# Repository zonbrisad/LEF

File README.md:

<div style="text-align: center">

# LEF (Lightweigth Event Framework)

</div>

<!-- START doctoc generated TOC please keep comment here to allow auto update -->
<!-- DON'T EDIT THIS SECTION, INSTEAD RE-RUN doctoc TO UPDATE -->

  - [About](#about)
  - [Features](#features)
  - [Requirements](#requirements)
    - [Runtime](#runtime)
    - [Development](#development)
  - [Install](#install)
    - [Download](#download)
    - [Installation](#installation)
  - [Freqlenty asked Questions](#freqlenty-asked-questions)
  - [Links](#links)
  - [Contribute](#contribute)
  - [License](#license)
  - [Some examples, remove after creation](#some-examples-remove-after-creation)
- [The largest heading](#the-largest-heading)
  - [The second largest heading](#the-second-largest-heading)
          - [The smallest heading](#the-smallest-heading)
  - [Tables](#tables)
  - [List](#list)
  - [Task list](#task-list)
  - [Colapsed section](#colapsed-section)
      - [We can hide anything, even code!](#we-can-hide-anything-even-code)
  - [Links](#links-1)

<!-- END doctoc generated TOC please keep comment here to allow auto update -->

## About

Lightweigth Event Framework (LEF) is a software framework for small to medium sized microcontrollers. It is intended for applications where an RTOS would be overkill, but still deliver some level of convenience.

## Features

Components for:
 - LED
 - RG LED
 - Buzzer
 - Click Button
 - Potentiometer
 - Rotary encoder (experimental)
 - Cli
 - Timers (software)
 - Eventloop
 - Eventqueue

## Requirements

### Runtime

### Development

## Install

### Download

### Installation

### Configuration

## Freqlenty asked Questions

## History

[HISTORY.md](/HISTORY.md)

## ToDo

- Some sort of sequence class could be usefull.
- Membrane button scanner
- Use C23 when available
- Helper functions for argument parsing in CLI
- Improved filtering out ANSI terminal sequences
- PWM component
- Error handling via messages
- Timed queue, where an queueelement is sent after a certain time

## Links

## Contribute

## License

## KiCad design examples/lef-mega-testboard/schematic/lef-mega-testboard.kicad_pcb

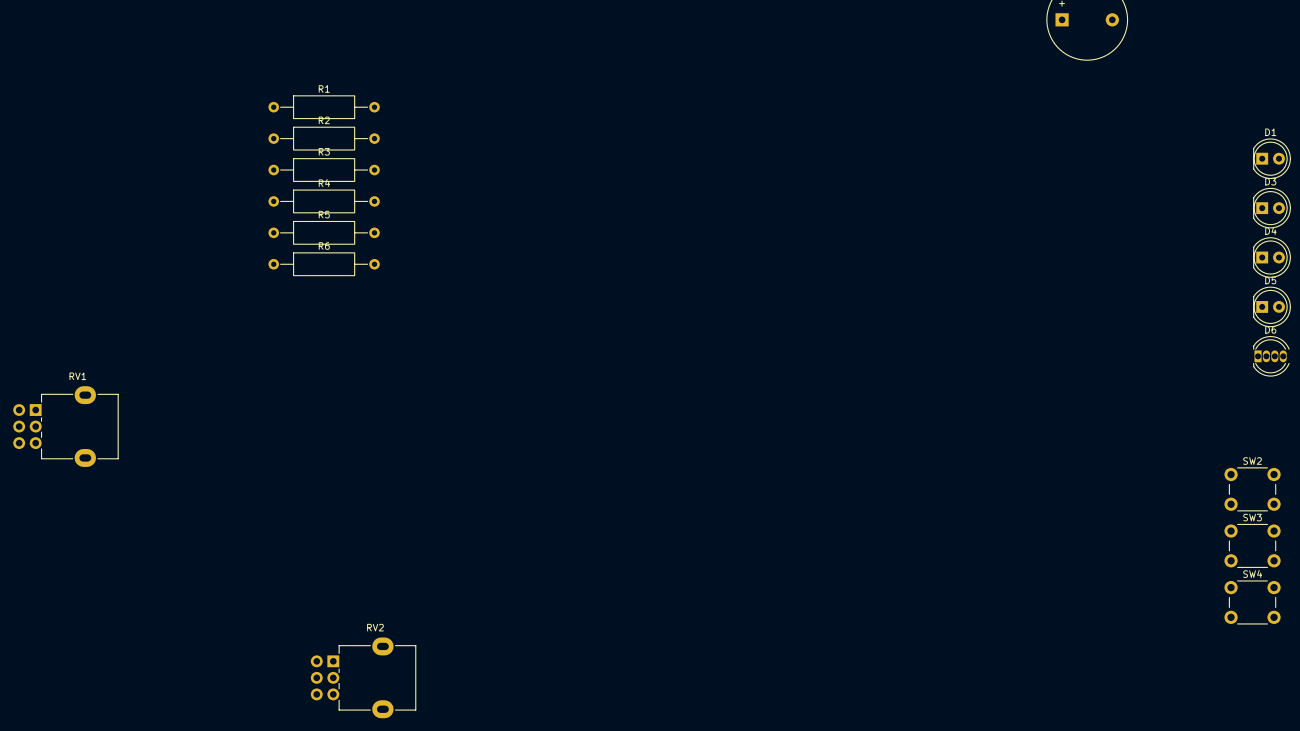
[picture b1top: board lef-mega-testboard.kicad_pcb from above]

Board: 2 copper layers, 17 parts (0 on the bottom side), 8 nets, no tracks yet.

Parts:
BZ1: Buzzer; Buzzer_12x9.5RM7.6
D1, D3, D4, D5: LED; LED_D5.0mm
D6: LED_Dual_AAK; LED_D5.0mm-4_RGB
R1, R2, R3, R4, R5, R6: 470; R_Axial_DIN0309_L9.0mm_D3.2mm_P15.24mm_Horizontal
RV1: 10k; Potentiometer_Alpha_RD902F-40-00D_Dual_Vertical
RV2: 10K; Potentiometer_Alpha_RD902F-40-00D_Dual_Vertical
SW2, SW3, SW4: SW_Push; SW_PUSH_6mm

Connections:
+5V: RV1.3, RV2.3
GND: BZ1.2 (-), D1.1 (K), D3.1 (K), D4.1 (K), D5.1 (K), R5.2, RV1.1, RV2.1, SW2.2, SW3.2, SW4.2
unnamed: BZ1.1 (+), R6.1
unnamed: D1.2 (A), R1.2
unnamed: D3.2 (A), R2.2
unnamed: D4.2 (A), R3.2
unnamed: D5.2 (A), R4.2
unnamed: D6.3 (K), R5.1

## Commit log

2016-07-15 Added new files
2016-11-30 Cleanup
2016-11-30 Added several new modules.
2016-11-30 Fixed bugs.
2016-12-06 Makefile upgrade.
2016-12-07 Added Eclipse project files.
2016-12-08 Updated template engine.
2016-12-08 Functions.
2016-12-09 Numerous changes.
2016-12-09 Added LED function + test.
2016-12-09 corrected ctemplate
2016-12-09 Added CLI
2016-12-13 Cli works
2016-12-13 Makefile
2016-12-16 Putting obect files in separate build directory
2016-12-19 Refactoring directory structure.
2016-12-20 Moved to examples
2016-12-20 Added symbolic link
2016-12-21 Added uart.c
2016-12-21 Added project files
2017-03-22 Added linux port.
2017-09-26 Numerous fixed
2017-09-27 Major cleanup
2023-01-27 Added management script
2023-01-27 Fixed rudimentary managing script
2023-04-14 Minor refactoring Added Button class
2023-04-14 Added
2023-04-14 Removed list files New gitignore
2023-04-15 Added Buzzer function Cleanup
2023-04-16 Basic cli operational More to be done, for example: backspace argument passing
2023-04-16 Added backspace support for cli
2023-04-16 Added some more comands
2023-04-17 Removed many warnings
2023-04-17 Changed error message printout for cli
2023-04-17 Added brp sound. Buzzer can be futher developed
2023-04-17 Fixed minor macro bug
2023-04-17 Restrucutred directories
2023-04-18 Completed LedRG
2023-04-18 Removed some old stuff
2023-04-18 Added LedRG Added Rotary
2023-04-19 Refactoring
    Moved standard queue to LEF.c
    Renamed API's
    Added event enum
    etc
2023-04-19 Fixed minor event handling bug.
2023-04-19 Some further refactoring
2023-04-19 adding example
2023-04-19 Added argument passing to cli. A separate buffer for argument might be needed in future
2023-04-24 Added custom beep mode.
2023-04-27 Api refactoring
2023-04-28 Added labels to Cli Some minor refactoring in CLI
2023-05-03 Added LEF_Pot
2023-05-08 Added Analog LED
2023-05-10 Added non blocking flash function
2023-05-10 Added async flashing function
2023-05-17 Added __PORT__
2024-06-03 Fixed init file
2025-04-22 Added loggo
2026-02-26 Added LED blink example Removed some compiler warnings
2026-02-26 Minor fixes
2026-02-26 Fixed compiler errors in simple example
2026-03-02 Added new mega example test
2026-03-02 Added Makefile
2026-03-02 Updated .gitignore
2026-03-03 Added files
2026-03-06 Fixed 4 led function Refactored code Updated schematic
2026-03-06 Schematic
2026-03-07 Refactoring, #pragma once Added double, tripple blink Refactored Led module
2026-03-07 Some minor fixes
2026-03-07 Some minor refactoring
2026-03-07 Fixed analog pot meter Fixed lefprint
2026-03-07 Reassigned buttons
2026-03-07 Did some cleanup/moves with files
2026-03-07 Added .editorconfig
2026-03-07 Fixed button problem
2026-03-07 Made some refactoring and updates to simple example
2026-03-08 New indentation set Red Green LED works
2026-03-08 Updated documentation Removed old stuff
2026-03-08 Basic LCD functions
2026-03-08 Added some LCD commands
2026-03-08 Code cleanup. Removed LEF_queue_element
2026-03-08 Added ANSI filter to CLi
2026-03-09 Added history to cli
2026-03-09 Adding cli
2026-03-09 Updated adcmon command
2026-03-09 Rewrite of LCD
2026-03-10 Major refactoring of lcd lib
2026-03-11 Another refactoring of lcd
2026-03-11 refactoring using new gpio macros
2026-03-11 Fixed minor Button bug.
2026-03-11 Updated simple example to modern gpio
2026-03-11 Updated ARDUIINO LED to gpio Other minor fixes
2026-03-12 Added .vscode settigns
2026-03-12 Fixed ADC MUX error Added enable function to LEF_Pot
2026-03-12 Minor bugfixes
2026-03-12 Fixed some examples
2026-03-13 Added LCD printout of pot value
2026-03-13 Fixed Cli History bug
2026-03-13 Removed printout in history
2026-03-14 Fixed argument filtering in CLI Updated Cli code to more robust
2026-03-14 Updated lef script with backup
2026-03-14 Removed example
2026-03-14 Update lef script
2026-03-14 Added CLI init macro
2026-03-14 Minor code cleanup
2026-03-14 Updated def Ipdated code with new int2bin
2026-03-14 Var updated
2026-03-14 Updated properties
2026-03-14 Memory optimization
2026-03-15 Memory opti
2026-03-15 Added new files Updated mptools
2026-03-16 Updated schematic
2026-03-17 Added digispark example
2026-03-17 Uppdated button Added new send command
2026-03-17 Updated CLI
2026-03-17 Ipdated pot
2026-03-17 Updated Rotary, need testing
2026-03-17 updated timer
2026-03-17 Added schematic
2026-03-18 Updated timer in simple
2026-03-18 Updating Timer in mega
2026-03-18 Rename
2026-03-18 System timer now output on pin 5
2026-03-18 Updated def Timer output added to pin
2026-03-18 Updated system timer
2026-03-18 Added 1ms interrupt using timer2 Updated def_avr for timer2 Fixed rotary encoder
2026-03-23 Added linux example
2026-03-23 Several updates
2026-03-23 Fixed some linux platform ussues
2026-03-24 Added basic Linux support, need more testing
2026-03-24 Fixed some issues with linux support Updated megatest
2026-03-24 Moved file
2026-03-25 Removed weird uart tree of files
2026-03-25 Added callback function for LCD gpio controll. Some minor fixed left, but working
2026-03-25 Refactoring of LCD.
2026-03-26 Added custom character example
2026-03-26 Added system information printout function
2026-03-27 Fixed LCD wrap
2026-03-28 Added generic 16 bit timer
2026-03-30 Added software i2c
2026-03-30 Added init_read/write function Added pcf functions
2026-03-30 pcf based LCD works, but slow
2026-03-30 New lcd functions
2026-03-30 Updated documentation for LCD driver
2026-03-31 Fixed LCD regression
2026-03-31 Adde support for TM1637 LED
2026-03-31 Refactoring, simplifying of code
2026-04-10 Fixed "reset" bug.
2026-04-11 Minor cleanup
2026-04-16 Uppdated managing script
2026-04-17 Updated LEF Updated Example with modern api Added button printout on LCD
2026-04-21 Added LEF_Core Fixed compiler warning
2026-04-21 Fixed simple example
2026-04-21 Code cleanup
2026-04-21 Updated spark example
2026-04-21 Updated blink example
2026-04-29 RP2040 port now working(not finished) Added RP Pico example
2026-05-05 Updated several Makefiles to handle concurrents targets Cleaned up Queue and Core
2026-05-05 Minor cleanup in lcd, i2c code
